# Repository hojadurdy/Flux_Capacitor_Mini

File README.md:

# Flux Capacitor Mini

### WHAT IS IT?
A miniature version of Flux Capacitor from the movie trilogy Back to the Future. Measuring at only 48mm x 38mm (1.89in x 1.5in), it can be easily pocketable . It is constructed with high quality 3D printed frame, sandwiched between stacked Gold Plated PCBs. Featuring 24 LEDs, diffused through bare FR4 material, that animate to create the “fluxxing” effect. It’s 100% decorative, it doesn’t actually let you travel through time. But let's not lose hope. Maybe in the future.

This mini Flux Capacitor is controlled by a Microchip ATtiny816 microcontroller. By using PWM (Pulse Width Modulation) pins for 8 channels of 3 paralleled LEDs, different animation patterns are generated for the fluxxxing effect. In settings mode, users are able change the animation type, speed, and LED brightness. There are 8 animations, 4 animation speeds, 4 LED brightness levels (100%, 75%, 50% and 25%).

### DEVICE SETTINGS
To set your desired animation, speed and LED brightness, you have to start flux condenser in Settings Mode. In order to do that, first you have to turn off your Flux Capacitor (if it's on) by holding "On/Off" button for 3 seconds **(you always have to hold the "On/Off" button for 3 seconds to turn it on or off)**. While holding the “Start/Set” button on the back turn the Flux Capacitor on by holing "On/Off" button for 3 seconds. You can release both buttons when you see all the LEDs start to light up one by one. Now you're in Settings Mode. Some of the LEDs should be on at full brightness and some very dimly lit (so you can see them through FR4 diffuser) according to the configuration it was set. LEDs on each row of all columns, starting from outer to inner are paralleled. LEDs are numbered as shown in the photo below to represent a setting for each LED.

The LEDs display the settings in binary. If it's fully lit then it is shows "on state or in binary 1" and if it's very dimly lit then it is shows "off state or 0 in binary". 
Now the combinations of the LEDs numbered 3, 2, and 1 sets your main animation. If you set those LEDs to different on/off states, you get 8 total combinations and on each set combination LEDs animate in different patterns.
LED number 4 displays setting for flashing animation which animates when you press "Start/Set" button in normal operation. With one LED you get only 2 combination either on or off.
LEDs numbered 5 and 6 displays the setting for animation speed. 2 LEDs make 4 total combinations. For each combination LEDs animate very slow, slow, fast or very fast.
LEDs numbered 7 and 8 displays the setting for LED brightness. For each of the 4 combinations LEDs light up at 25%, 50%, 75% or 100%.
All of the combinations, and setting examğles are shown in the tables below.

You don't have to remember these. There is a QR code on the interior side of back cover PCB. Scan it and it will take you to this page.
To change the LED state, while in Settings Mode, hold the "Start/Set" button. All the LEDs should be turned on very dimly and second after that, starting from LED1 each individual LED gets fully lit. Hold the "Start/Set" button until the fully lit LED reaches the one you want to change. When you change the LED state, if the LED is already set on, it turns off (or dimly lit). If it's at off state (or dimly lit) then it turns on at full brightness. 
If all of this feels complicated to you then I can program the Flux Capacitor with older much simpler version of the firmware by your request. But the older firmware has less functionality. Check it **[HERE](https://www.youtube.com/watch?v=2X2gqoI-mSA)**

You don't have to remember these. There is a QR code on the interior side of back cover PCB. Scan it and it will take you to this page.

Below, all of the LED animations and their LED setting combinations are shown. Also animation patterns might seem different when you run them at different speeds.

https://user-images.githubusercontent.com/43648325/163351795-e4758084-3ac4-411a-833b-632b1832e1c3.mov

https://user-images.githubusercontent.com/43648325/163351857-c6b9a43f-3085-4918-af22-fd343d08b809.mov

https://user-images.githubusercontent.com/43648325/163352711-5db71f97-86e2-47c3-9c65-f71232630f72.mov

https://user-images.githubusercontent.com/43648325/163353298-47ecd2d0-05f4-4908-87b2-38960816e004.mov

### POWER REQUIREMENT
Device requires 1.21 Gigawatts ("Jigowatts") of power to operate. That amount of power is no match for an ordinary power supply. Luckily we've developed a miniature nuclear reactor named LIR2032 that needs to be placed inside the device. LIR2032 also encapsulates a small pellet of Plutonium to be used as fuel to generate enough power. This miniature reactor is able to supply all the power required for the Flux Capacitor. Ok, joke aside this entire paragraph is totally not true.

To really power it, you only need a non-rechargeable CR2032 or rechargeable LIR2032 coin cell battery. Power consumption is drastically lowered. At full brightness, it draws 3.7mA and at 25% brightness it draws 1.8mA of current from the battery. 

CR2032 (Non-Rechargeable) with average of 210mAh battery capacity.

- 100% LED Brightness :  57 Hours
- 25%  LED Brightness :  110 Hours

LIR2032 (Rechargeable) with average of 40mAh battery capacity.

- 100% LED Brightness :  11 Hours
- 25%  LED Brightness :  21 Hours

### WHAT MAKES THIS DEVICE SPECIAL?
First of all, the gold plating on the PCB makes it look luxurious. You can wear it around your neck with an ID card strap, hang it on your keychain or... you can place it on your car's dashboard and try and see if the time travel is possible while you're driving at 88mph. Time travel at your own RISK! If you stuck in unknown territories of time, try turning on the SOS mode of the Flux Capacitor (Animation 5 or 101 LED combination). Help may or may not arrive. NO GUARANTEES.

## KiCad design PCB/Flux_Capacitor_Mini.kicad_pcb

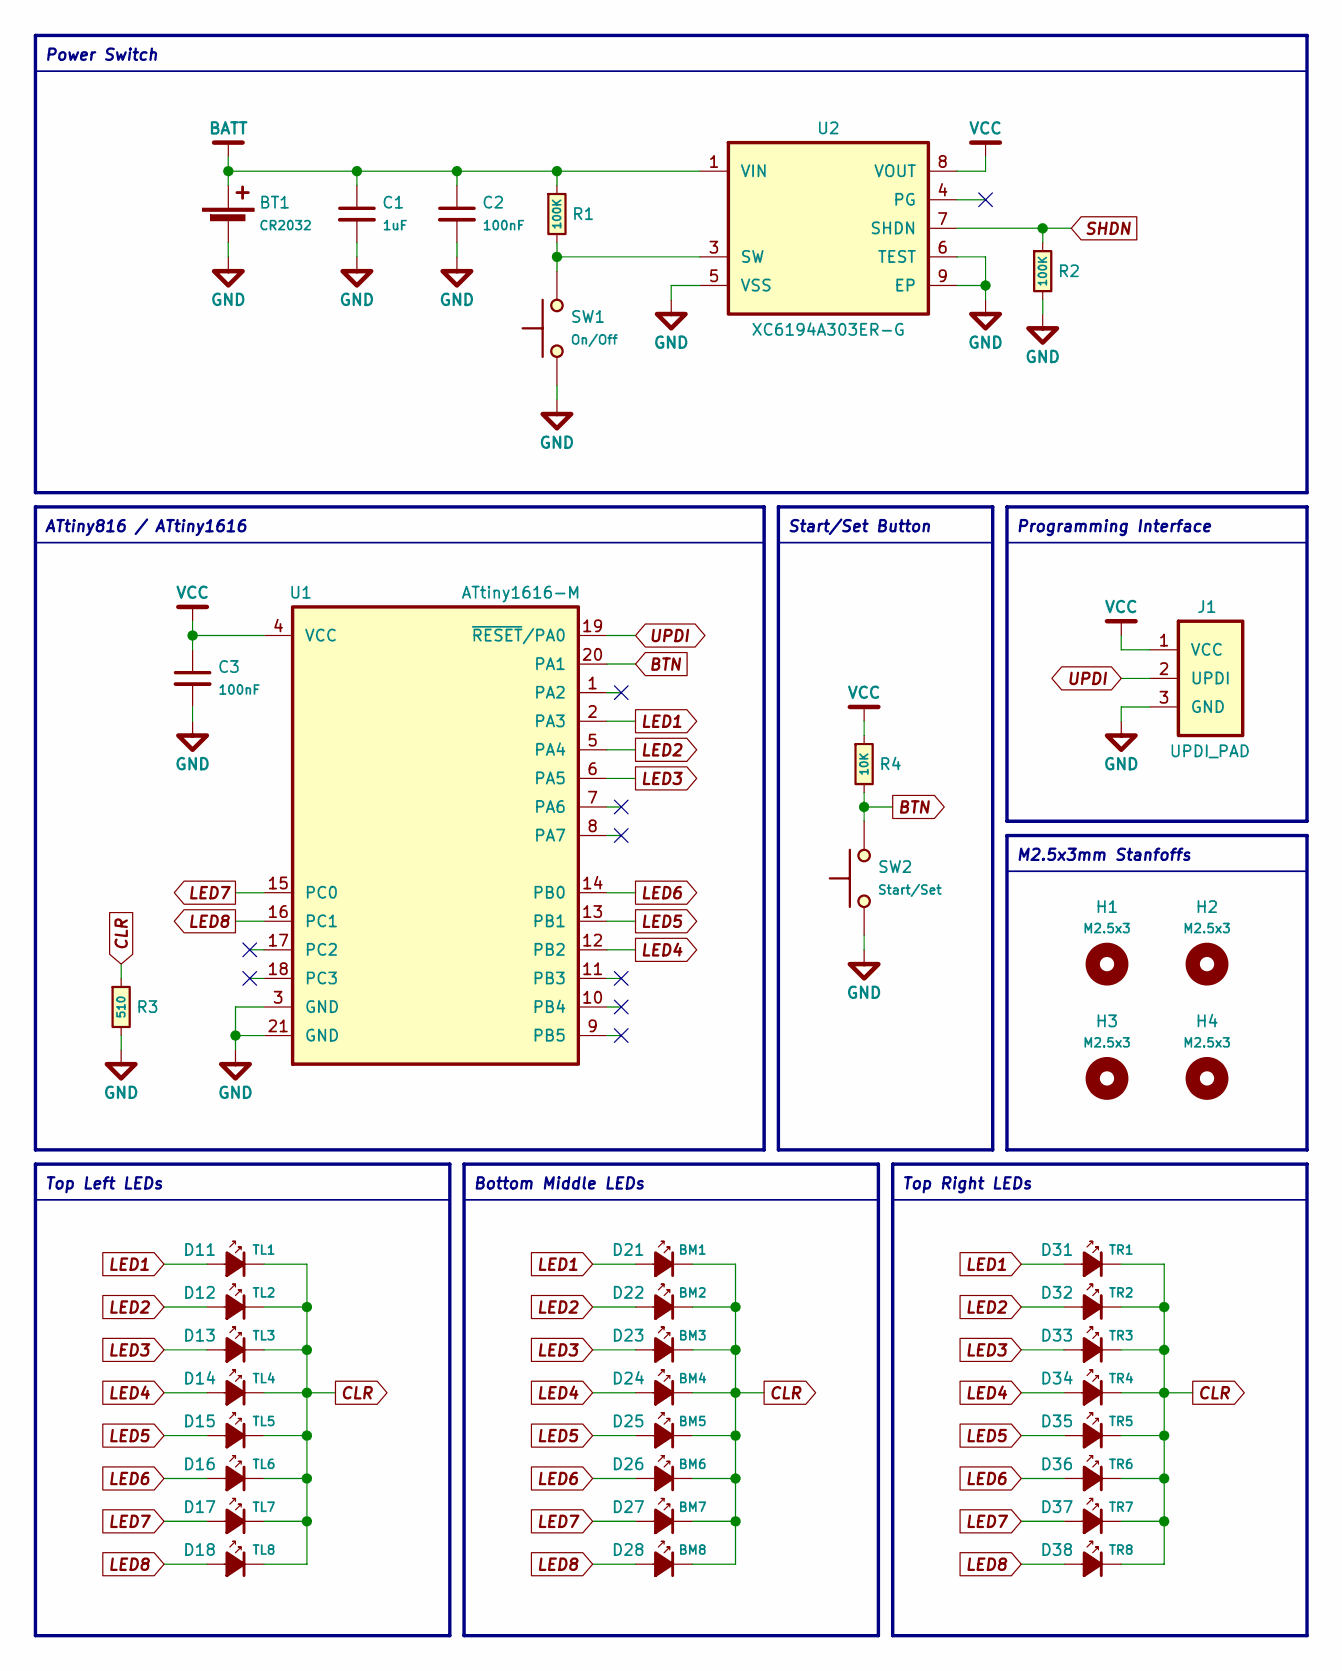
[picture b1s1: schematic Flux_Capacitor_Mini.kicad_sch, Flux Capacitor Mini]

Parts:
BT1: CR2032; CR2032_MY-FJ-113LM_MY-ZJ-110
C1: 1uF; C_0402_1005Metric
C2, C3: 100nF; C_0402_1005Metric
D11: TL1; LED_0603_1608Metric
D12: TL2; LED_0603_1608Metric
D13: TL3; LED_0603_1608Metric
D14: TL4; LED_0603_1608Metric
D15: TL5; LED_0603_1608Metric
D16: TL6; LED_0603_1608Metric
D17: TL7; LED_0603_1608Metric
D18: TL8; LED_0603_1608Metric
D21: BM1; LED_0603_1608Metric
D22: BM2; LED_0603_1608Metric
D23: BM3; LED_0603_1608Metric
D24: BM4; LED_0603_1608Metric
D25: BM5; LED_0603_1608Metric
D26: BM6; LED_0603_1608Metric
D27: BM7; LED_0603_1608Metric
D28: BM8; LED_0603_1608Metric
D31: TR1; LED_0603_1608Metric
D32: TR2; LED_0603_1608Metric
D33: TR3; LED_0603_1608Metric
D34: TR4; LED_0603_1608Metric
D35: TR5; LED_0603_1608Metric
D36: TR6; LED_0603_1608Metric
D37: TR7; LED_0603_1608Metric
D38: TR8; LED_0603_1608Metric
H1, H2, H3, H4: M2.5x3; SMTSO2530CTJ
J1: UPDI_PAD; PogoPad_1x03_P1.27mm
R1, R2: 100K; R_0402_1005Metric
R3: 510; R_0402_1005Metric
R4: 10K; R_0402_1005Metric
SW1: On/Off; SW_SPST_4.5x4.5mm
SW2: Start/Set; SW_SPST_4.5x4.5mm
U1: ATtiny1616-M; VQFN-20-1EP_3x3mm_P0.4mm_EP1.7x1.7mm
U2: XC6194A303ER-G; USP-8B06_2.0x2.0mm_P0.5mm_EP1.0x1.8mm

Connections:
BATT: BT1.1 (+), C1.1, C2.1, R1.1, U2.1 (VIN)
BTN: R4.2, SW2.2, U1.20 (PA1)
CLR: D11.1 (K), D12.1 (K), D13.1 (K), D14.1 (K), D15.1 (K), D16.1 (K), D17.1 (K), D18.1 (K), D21.1 (K), D22.1 (K), D23.1 (K), D24.1 (K), D25.1 (K), D26.1 (K), D27.1 (K), D28.1 (K), D31.1 (K), D32.1 (K), D33.1 (K), D34.1 (K), D35.1 (K), D36.1 (K), D37.1 (K), D38.1 (K), R3.1
GND: BT1.2 (-), C1.2, C2.2, C3.2, J1.3 (GND), R2.2, R3.2, SW1.1, SW2.1, U1.3 (GND), U1.21 (GND), U2.5 (VSS), U2.6 (TEST), U2.9 (EP)
LED1: D11.2 (A), D21.2 (A), D31.2 (A), U1.2 (PA3)
LED2: D12.2 (A), D22.2 (A), D32.2 (A), U1.5 (PA4)
LED3: D13.2 (A), D23.2 (A), D33.2 (A), U1.6 (PA5)
LED4: D14.2 (A), D24.2 (A), D34.2 (A), U1.12 (PB2)
LED5: D15.2 (A), D25.2 (A), D35.2 (A), U1.13 (PB1)
LED6: D16.2 (A), D26.2 (A), D36.2 (A), U1.14 (PB0)
LED7: D17.2 (A), D27.2 (A), D37.2 (A), U1.15 (PC0)
LED8: D18.2 (A), D28.2 (A), D38.2 (A), U1.16 (PC1)
unnamed: R1.2, SW1.2, U2.3 (SW)
SHDN: R2.1, U2.7 (SHDN)
UPDI: J1.2 (UPDI), U1.19 (~RESET/PA0)
VCC: C3.1, J1.1 (VCC), R4.1, U1.4 (VCC), U2.8 (VOUT)

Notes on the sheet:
ATtiny816 / ATtiny1616
Bottom Middle LEDs
Start/Set Button
Top Right LEDs
M2.5x3mm Stanfoffs
Programming Interface
Top Left LEDs
Power Switch

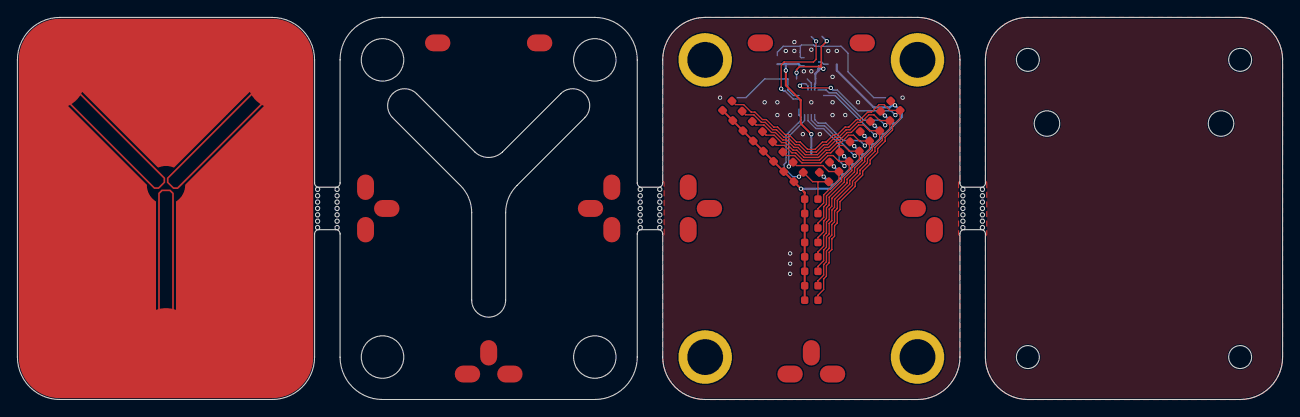
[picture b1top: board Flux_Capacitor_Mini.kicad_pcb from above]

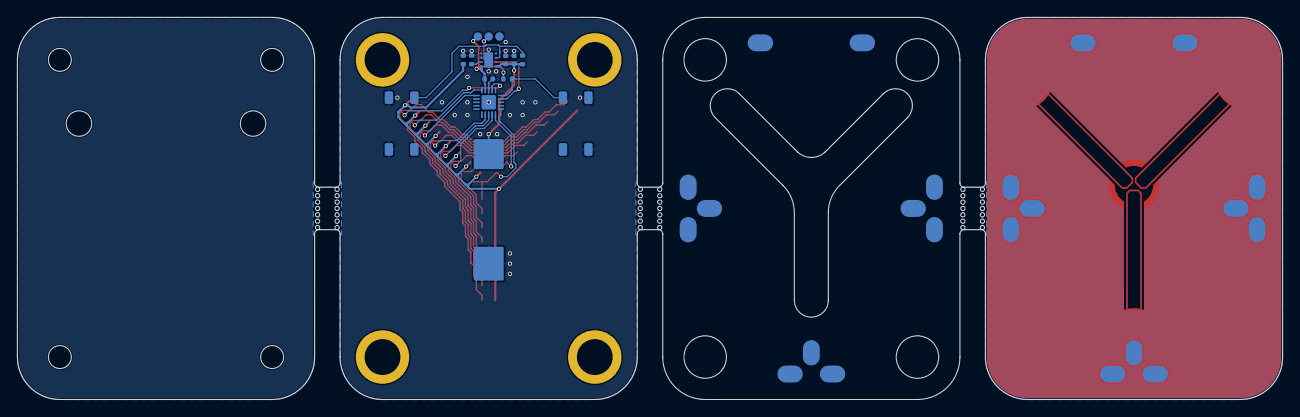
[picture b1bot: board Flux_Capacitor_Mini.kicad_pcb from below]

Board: 2 copper layers, 149.0 x 45.0 mm, 53 parts (29 on the bottom side), 16 nets.

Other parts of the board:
kibuzzard-62311D83, kibuzzard-62311D83#2: G***; kibuzzard-62311D83
kibuzzard-62327BD2: G***; kibuzzard-62327BD2
kibuzzard-62327D38: G***; kibuzzard-62327D38
kibuzzard-62330E41: G***; kibuzzard-62330E41
kibuzzard-623256DE: G***; kibuzzard-623256DE
kibuzzard-623278F0: G***; kibuzzard-623278F0
kibuzzard-6232791A: G***; kibuzzard-6232791A
kibuzzard-62327207: G***; kibuzzard-62327207
kibuzzard-62327418: G***; kibuzzard-62327418
kibuzzard-62327445: G***; kibuzzard-62327445
kibuzzard-62327907: G***; kibuzzard-62327907

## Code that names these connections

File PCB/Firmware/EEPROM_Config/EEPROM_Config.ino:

#include <EEPROM.h>

//------ PIN DEFINITIONS ------//

#define led1    16
#define led2    0
#define led3    1
#define led4    7
#define led5    8
#define led6    9
#define led7    10
#define led8    11
#define button  14

//-- BUTTON HOLD TIME PRESETS --//

//Counter Value
float pressLength_ms = 0;

//Main Animation Sequence - 3bit
#define main_animation1     1000     //LSB   1 Second
#define main_animation2     2000     //      2 Seconds
#define main_animation4     3000     //MSB   3 Seconds

//Flash Animation Sequence - 1bit
#define flash_animation1    4000     //      4 Seconds

//Animation Speed - 2bit
#define speed1              5000     //LSB   5 Seconds
#define speed2              6000     //MSB   6 Seconds

//LED Brightness - 2bit
#define brightness1         7000     //LSB   7 Seconds
#define brightness2         8000     //MSB   8 Seconds

//-- SETTINGS EEPROM ADDRESS --//

#define main_animation1_addr    11
#define main_animation2_addr    12
#define main_animation4_addr    13
#define flash_animation1_addr   14
#define speed1_addr             15
#define speed2_addr             16
#define brightness1_addr        17
#define brightness2_addr        18

byte main_animation1_val;
byte main_animation2_val;
byte main_animation4_val;
byte flash_animation1_val;
byte speed1_val;
byte speed2_val;
byte brightness1_val;
byte brightness2_val;

//-----------------------------//

int buttonState = 1;      //Button state while not being pressed. When pressed pulls pin to GND.

byte startup;
byte startUpState;
byte startUpMode;
byte main_animationSequence;
byte flash_animationSequence;
byte animationSpeed;
byte ledBrightness;

void setup() {               
    pinMode(led1, OUTPUT); 
    pinMode(led2, OUTPUT);
    pinMode(led3, OUTPUT);
    pinMode(led4, OUTPUT);
    pinMode(led5, OUTPUT);
    pinMode(led6, OUTPUT);
    pinMode(led7, OUTPUT);
    pinMode(led8, OUTPUT); 
    pinMode(button, INPUT);   

    EEPROM.write(1, 1);
    EEPROM.write(11, 0);
    EEPROM.write(12, 0);
    EEPROM.write(13, 0);
    EEPROM.write(14, 0);
    EEPROM.write(15, 0);
    EEPROM.write(16, 1);
    EEPROM.write(17, 0);
    EEPROM.write(18, 0);
}

void loop() {
    startUpSequence();
    
    analogWrite(led1, ledBrightness);
    delay(animationSpeed*2);
    checkButton();
    analogWrite(led2, ledBrightness);
    delay(animationSpeed*2);
    checkButton();
    analogWrite(led3, ledBrightness);
    delay(animationSpeed*2);
    checkButton();
    analogWrite(led4, ledBrightness);
    delay(animationSpeed*2);
    checkButton();
    analogWrite(led5, ledBrightness);
    delay(animationSpeed*2);
    checkButton();
    analogWrite(led6, ledBrightness);
    delay(animationSpeed*2);
    checkButton();
    analogWrite(led7, ledBrightness);
    delay(animationSpeed*2);
    checkButton();
    analogWrite(led8, ledBrightness);
    delay(animationSpeed*2);
    checkButton();
}

void startUpSequence() {
    startUpMode = EEPROM.read(1);
    main_animation1_val = EEPROM.read(main_animation1_addr);
    main_animation2_val = EEPROM.read(main_animation2_addr);
    main_animation4_val = EEPROM.read(main_animation4_addr);
    flash_animation1_val = EEPROM.read(flash_animation1_addr);
    speed1_val = EEPROM.read(speed1_addr);
    speed2_val = EEPROM.read(speed2_addr);
    brightness1_val = EEPROM.read(brightness1_addr);
    brightness2_val = EEPROM.read(brightness2_addr);

    if(startUpMode == 0 && digitalRead(button) == 0 && startup == 1) {
        analogWrite(led1, 200);
        delay(150);
        analogWrite(led2, 200);
        delay(150);
        analogWrite(led3, 200);
        delay(150);
        analogWrite(led4, 200);
        delay(150);
        analogWrite(led5, 200);
        delay(150);
        analogWrite(led6, 200);
        delay(150);
        analogWrite(led7, 200);
        delay(150);
        analogWrite(led8, 200);
        delay(150);

        startup = 0;
    }
    else {
      //Do Nothing
    }

    //Determine Main Animation Sequence According to Values from 3 EEPROM Addresses
    if(main_animation4_val == 0 && main_animation2_val == 0 && main_animation1_val == 0) {
        main_animationSequence = 1;
    }
    else if(main_animation4_val == 0 && main_animation2_val == 0 && main_animation1_val == 1) {
        main_animationSequence = 2;
    }
    else if(main_animation4_val == 0 && main_animation2_val == 1 && main_animation1_val == 0) {
        main_animationSequence = 3;
    }
    else if(main_animation4_val == 0 && main_animation2_val == 1 && main_animation1_val == 1) {
        main_animationSequence = 4;
    }
    else if(main_animation4_val == 1 && main_animation2_val == 0 && main_animation1_val == 0) {
        main_animationSequence = 5;
    }
    else if(main_animation4_val == 1 && main_animation2_val == 0 && main_animation1_val == 1) {
        main_animationSequence = 6;
    }
    else if(main_animation4_val == 1 && main_animation2_val == 1 && main_animation1_val == 0) {
        main_animationSequence = 7;
    }
    else if(main_animation4_val == 1 && main_animation2_val == 1 && main_animation1_val == 1) {
        main_animationSequence = 8;
    }

    //Determine Flash Animation Sequence According to Value from EEPROM Address
    if(flash_animation1_val == 0) {
        flash_animationSequence = 1;
    }
    else if(flash_animation1_val == 1) {
        flash_animationSequence = 2;
    }

    //Determine Animation Speed According to Values from 2 EEPROM Addresses
    if(speed2_val == 0 && speed1_val == 0) {
        animationSpeed = 100;
    }
    else if(speed2_val == 0 && speed1_val == 1) {
        animationSpeed = 75;
    }
    else if(speed2_val == 1 && speed1_val == 0) {
        animationSpeed = 50;
    }
    else if(speed2_val == 1 && speed1_val == 1) {
        animationSpeed = 25;
    }

    //Determine LED Brightness According to Values from 2 EEPROM Addresses
    if(brightness2_val == 0 && brightness1_val == 0) {
        ledBrightness = 63;
    }
    else if(brightness2_val == 0 && brightness1_val == 1) {
        ledBrightness = 127;
    }
    else if(brightness2_val == 1 && brightness1_val == 0) {
        ledBrightness = 191;
    }
    else if(brightness2_val == 1 && brightness1_val == 1) {
        ledBrightness = 255;
    }
}

void checkButton(){
    while (digitalRead(button) == LOW ){ 
        analogWrite(led1, ledBrightness);
        analogWrite(led2, 0);
        analogWrite(led3, ledBrightness);
        analogWrite(led4, 0);
        analogWrite(led5, ledBrightness);
        analogWrite(led6, 0);
        analogWrite(led7, ledBrightness);
        analogWrite(led8, 0);
    }
}

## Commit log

2022-04-13 Rename LICENSE.md to CC-BY-NC-SA-4.0.md
2022-04-13 Rename CC-BY-NC-SA-4.0.md to LICENSE.md
